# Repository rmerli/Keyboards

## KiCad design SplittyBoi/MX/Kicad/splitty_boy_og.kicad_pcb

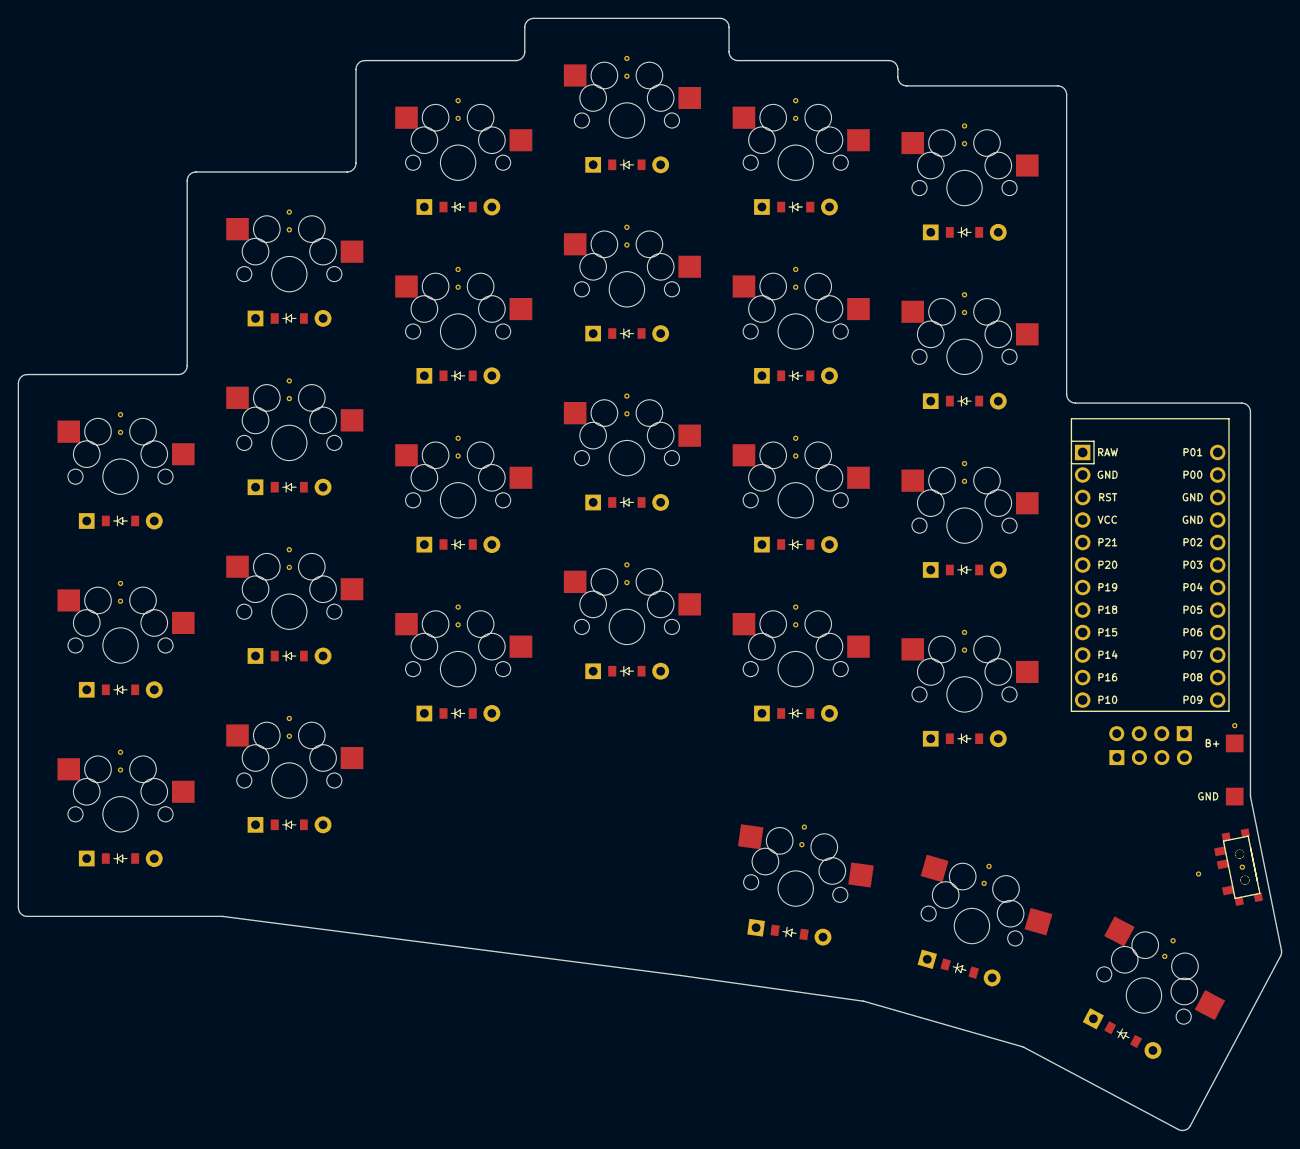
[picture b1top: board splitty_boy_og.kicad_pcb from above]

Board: 2 copper layers, 142.6 x 125.5 mm, 59 parts (0 on the bottom side), 43 nets, no tracks yet.

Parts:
D1, D2, D3, D4, D5, D6, D7, D8, D9, D10, D11, D12, D13, D14, D15, D16, D17, D18, D19, D20, D21, D22, D23, D24, D25, D26: ComboDiode
MCU1: ProMicro
OLED1, OLED2: OLED; OLED_headers
PAD1, PAD2: SMDPad
S1, S2, S3, S4, S5, S6, S7, S8, S9, S10, S11, S12, S13, S14, S15, S16, S17, S18, S19, S20, S21, S22, S23, S24, S25, S26: MX
T1, T2: SPDT_C128955

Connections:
B+: PAD1.1, T1.2, T2.2
GND: MCU1.2, MCU1.15, MCU1.16, OLED1.1, OLED2.1, PAD2.1
P2: MCU1.17, OLED1.4, OLED2.4
P3: MCU1.18, OLED1.3, OLED2.3
P4: MCU1.19, S1.1, S2.1, S3.1
P5: MCU1.20, S4.1, S5.1, S6.1, S7.1
P6: MCU1.21, S8.1, S9.1, S10.1, S11.1
P7: MCU1.22, S12.1, S13.1, S14.1, S15.1, S24.1
P8: MCU1.23, S16.1, S17.1, S18.1, S19.1, S25.1
P9: MCU1.24, S20.1, S21.1, S22.1, S23.1, S26.1
P16: D24.1, D25.1, D26.1, MCU1.11
P18: D1.1, D4.1, D8.1, D12.1, D16.1, D20.1, MCU1.8
P19: D2.1, D5.1, D9.1, D13.1, D17.1, D21.1, MCU1.7
P20: D3.1, D6.1, D10.1, D14.1, D18.1, D22.1, MCU1.6
P21: D7.1, D11.1, D15.1, D19.1, D23.1, MCU1.5
RAW: MCU1.1, T1.1, T2.1
VCC: MCU1.4, OLED1.2, OLED2.2
index_bottom: D16.2, S16.2
index_home: D17.2, S17.2
index_numbers: D19.2, S19.2
index_top: D18.2, S18.2
inner_bottom: D20.2, S20.2
inner_home: D21.2, S21.2
inner_numbers: D23.2, S23.2
inner_top: D22.2, S22.2
inny_fan: D24.2, S24.2
middle_bottom: D12.2, S12.2
middle_home: D13.2, S13.2
middle_numbers: D15.2, S15.2
middle_top: D14.2, S14.2
pinky_bottom: D4.2, S4.2
pinky_home: D5.2, S5.2
pinky_numbers: D7.2, S7.2
pinky_top: D6.2, S6.2
reachy_fan: D26.2, S26.2
ring_bottom: D8.2, S8.2
ring_home: D9.2, S9.2
ring_numbers: D11.2, S11.2
ring_top: D10.2, S10.2
shifty_bottom: D1.2, S1.2
shifty_home: D2.2, S2.2
shifty_top: D3.2, S3.2
tucky_fan: D25.2, S25.2

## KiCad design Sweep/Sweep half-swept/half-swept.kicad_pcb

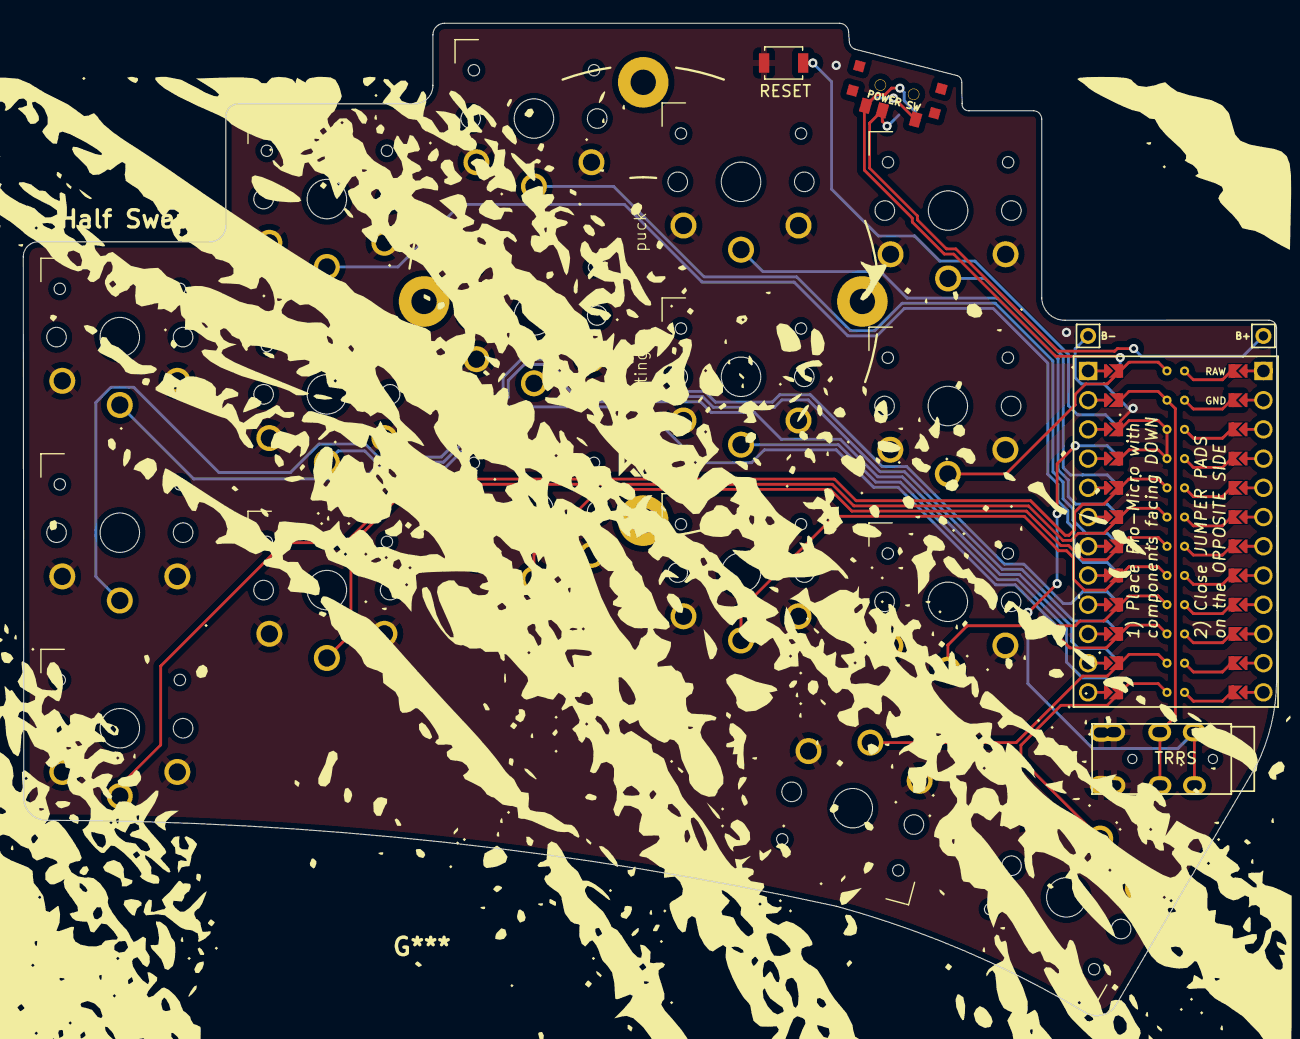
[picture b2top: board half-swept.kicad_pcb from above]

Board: 2 copper layers, 109.0 x 86.3 mm, 23 parts (0 on the bottom side), 23 nets.

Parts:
B+: MountingHole_Pad; 1pin_conn
B-: MountingHole_Pad; 1pin_conn
J2: AudioJack4dpb; TRRS-PJ-DPB2
POWER SW: SW_SPDT; SPDT_C128955
RSW2: SW_Push; Tactile-Switch_SMT
SW1, SW2, SW3, SW4, SW5, SW6, SW7, SW8, SW9, SW10, SW11, SW12, SW13, SW14, SW15, SW16, SW17: SW_Push; SW_PG1350_rev_DPB
U1: ProMicro-kbd; ProMicro_jumpers_facedown

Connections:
BT+_r: B+.1, POWER SW.2
Switch1: SW1.1, U1.10
Switch2: SW2.1, U1.17
Switch3: SW3.1, U1.18
Switch4: SW4.1, U1.19
Switch5: SW5.1, U1.20
Switch6: SW6.1, U1.16
Switch7: SW7.1, U1.15
Switch8: SW8.1, U1.14
Switch9: SW9.1, U1.13
Switch10: SW10.1, U1.1
Switch11: SW11.1, U1.5
Switch12: SW12.1, U1.6
Switch13: SW13.1, U1.7
Switch14: SW14.1, U1.8
Switch15: SW15.1, U1.9
Switch16: SW16.1, U1.11
Switch17: SW17.1, U1.12
Switch18: J2.R1, U1.2
gnd: B-.1, J2.S, J2.T, RSW2.1, RSW2.2, SW1.2, SW2.2, SW3.2, SW4.2, SW5.2, SW6.2, SW7.2, SW8.2, SW9.2, SW10.2, SW11.2, SW12.2, SW13.2, SW14.2, SW15.2, SW16.2, SW17.2, U1.3, U1.4, U1.23
raw: POWER SW.3, U1.24
reset: RSW2.1, RSW2.2, U1.22
vcc: J2.R2, U1.21

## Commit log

2024-04-03 moved to unified
2024-04-03 added sweep config
2024-04-04 added more projects
2024-04-05 added choc variant for splittyboi
